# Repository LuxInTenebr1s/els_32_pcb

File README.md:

# els_32_pcb
ELS32 LED strip Ethernet controller with LAN8720 on PHY level.

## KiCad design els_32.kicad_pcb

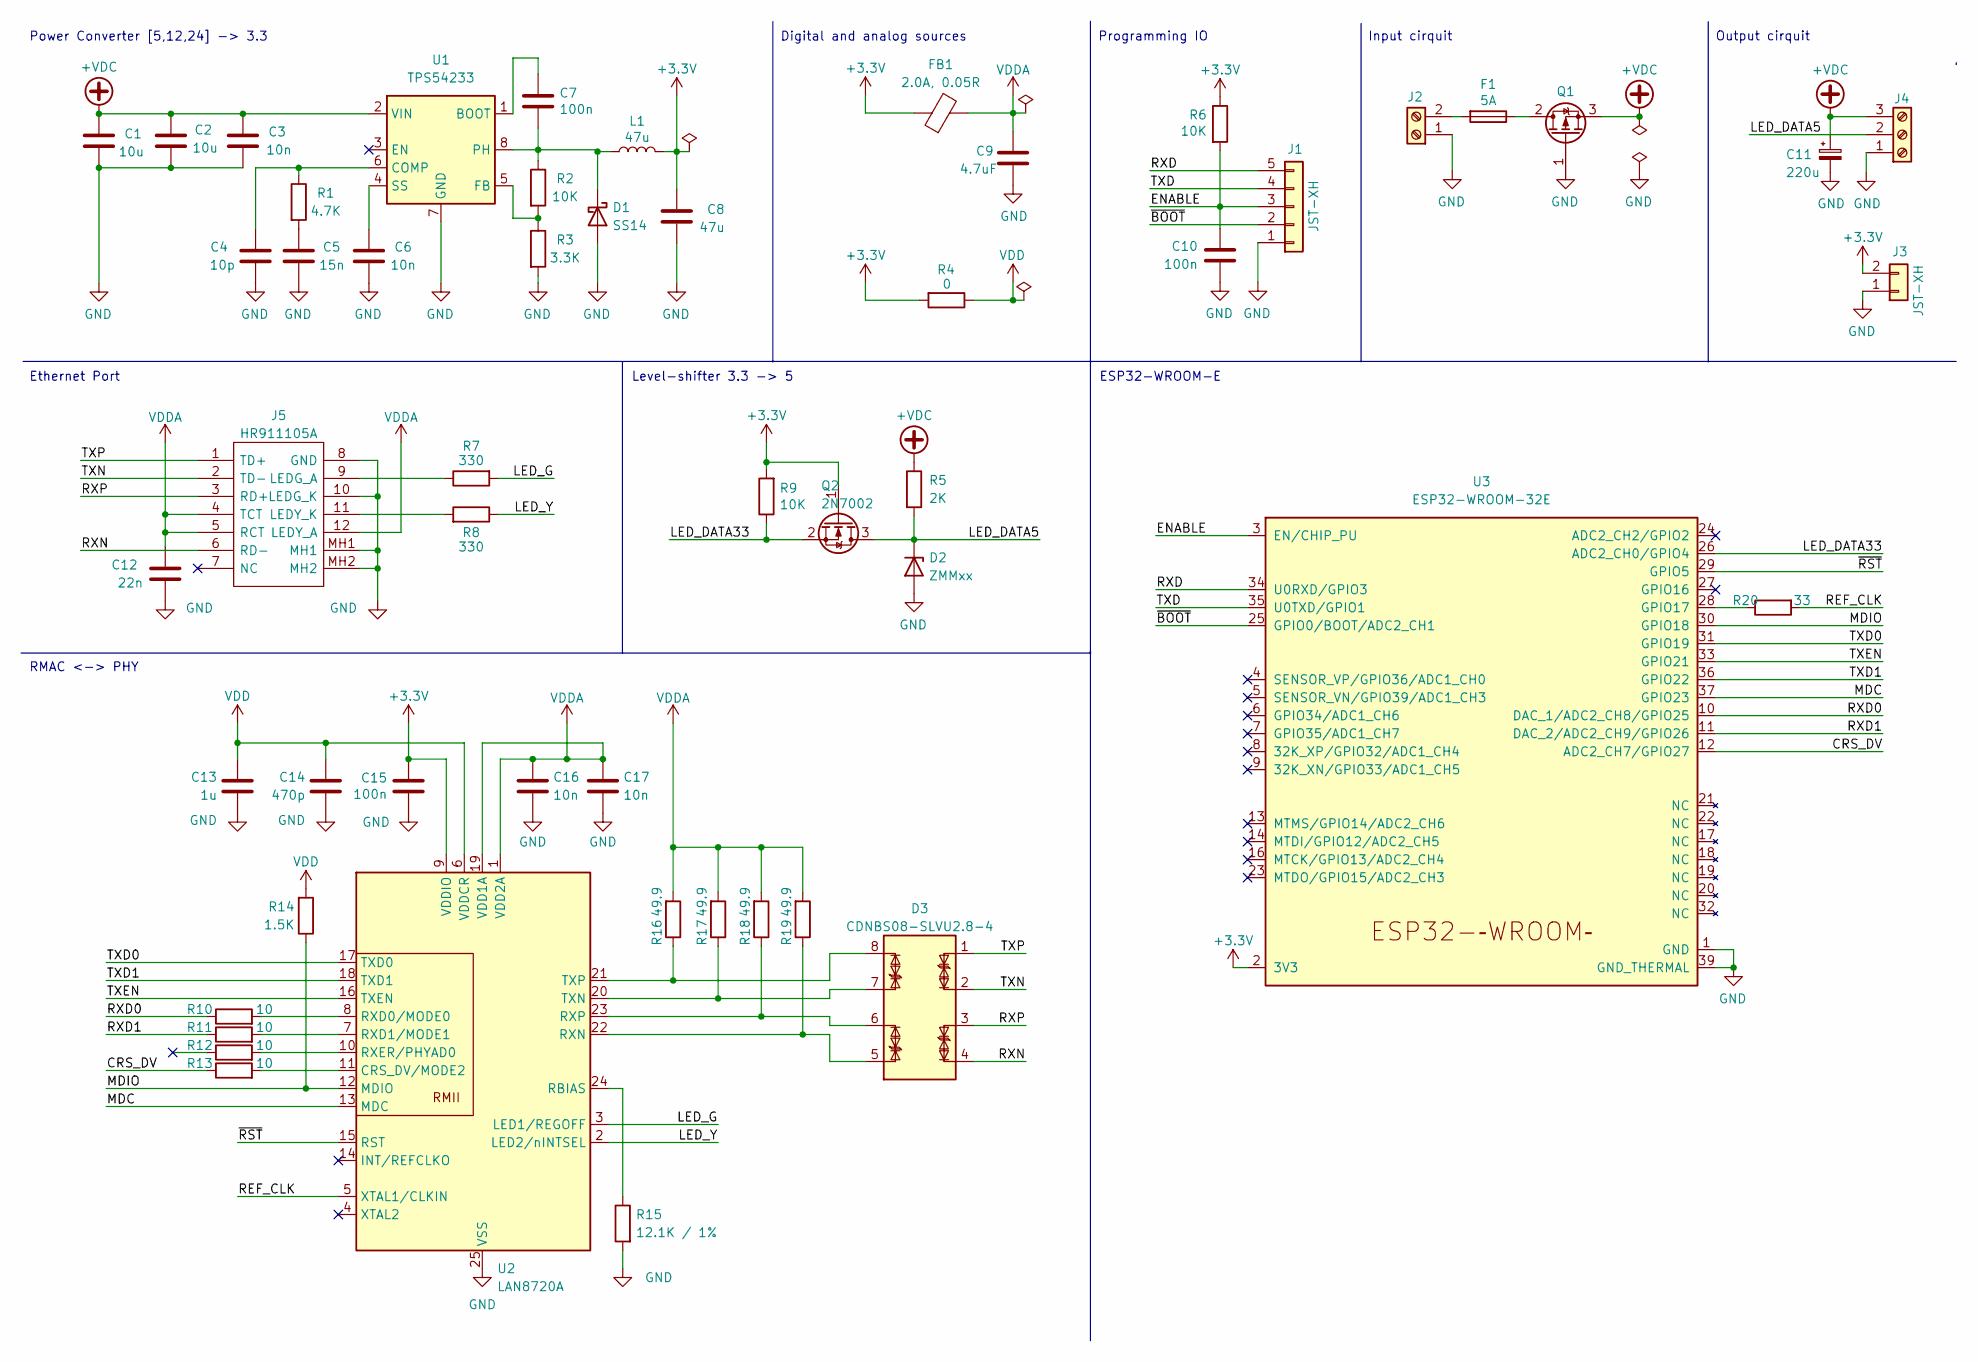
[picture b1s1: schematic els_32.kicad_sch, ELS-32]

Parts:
C1, C2: 10u; C_1206_3216Metric; LCSC C13585
C3, C6, C16, C17: 10n; C_0402_1005Metric; LCSC C15195
C4: 10p; C_0603_1608Metric; LCSC C1634
C5: 15n; C_0603_1608Metric; LCSC C1596
C7, C10, C15: 100n; C_0402_1005Metric; LCSC C307331
C8: 47u; C_1206_3216Metric; LCSC C96123
C9: 4.7uF; C_0402_1005Metric; LCSC C23733
C11: 220u; CP_Elec_6.3x7.7; LCSC C127327
C12: 22n; C_0402_1005Metric; LCSC C1532
C13: 1u; C_0402_1005Metric; LCSC C52923
C14: 470p; C_0402_1005Metric; LCSC C1537
D1: SS14; D_SMA; LCSC C2480
D2: ZMMxx; D_MiniMELF; LCSC C8062
D3: CDNBS08-SLVU2.8-4; SOIC-8_3.9x4.9mm_P1.27mm; LCSC C2841839
F1: 5A; Fuseholder_Littelfuse_Nano2_154x; LCSC C108518
FB1: 2.0A, 0.05R; R_0603_1608Metric; LCSC C275484
J1: JST-XH; JST_XH_B5B-XH-A_1x05_P2.50mm_Vertical
J2: WAGO; TerminalBlock_WAGO_236-102_1x02_P5.00mm_45Degree
J3: JST-XH; JST_XH_B2B-XH-AM_1x02_P2.50mm_Vertical
J4: Conn_01x03_Female; TerminalBlock_WAGO_236-103_1x03_P5.00mm_45Degree
J5: HR911105A; Manufacturer_Part_Number HR911105A; LCSC C12074
L1: 47u; L_Sunlord_MWSA06xxS; LCSC C408471
Q1: Q_PMOS_DGS; SOT-23; LCSC C20917
Q2: 2N7002; SOT-23; LCSC C8545
R1: 4.7K; R_0402_1005Metric; LCSC C25900
R2, R6, R9: 10K; R_0402_1005Metric; LCSC C25744
R3: 3.3K; R_0402_1005Metric; LCSC C25890
R4: 0; R_1206_3216Metric; LCSC C17888
R5: 2K; R_1206_3216Metric; LCSC C17944
R7, R8: 330; R_0402_1005Metric; LCSC C25104
R10, R11, R12, R13: 10; R_0402_1005Metric; LCSC C25077
R14: 1.5K; R_0402_1005Metric; LCSC C25867
R15: 12.1K / 1%; R_0402_1005Metric; LCSC C25852
R16, R17, R18, R19: 49.9; R_0402_1005Metric; LCSC C25120
R20: 33; R_0402_1005Metric; LCSC C25105
U1: TPS54233; SOIC-8_3.9x4.9mm_P1.27mm; LCSC C9865
U2: LAN8720A; QFN-24-1EP_4x4mm_P0.5mm_EP2.6x2.6mm; LCSC C17146
U3: ESP32-WROOM-32E; LCSC C701342

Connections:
+3.3V: C8.2, C15.1, FB1.1, J3.2, L1.2, Q2.1 (G), R4.2, R6.1, R9.2, U2.9 (VDDIO), U3.2 (3V3)
+VDC: C1.2, C2.1, C3.2, C11.1, J4.3, Q1.3 (S), R5.1, U1.2 (VIN)
/CRS_DV: R13.1, U3.12 (ADC2_CH7/GPIO27)
/ENABLE: C10.2, J1.3, R6.2, U3.3 (EN/CHIP_PU)
/LED_DATA5: D2.1 (K), J4.2, Q2.3 (D), R5.2
/LED_DATA33: Q2.2 (S), R9.1, U3.26 (ADC2_CH0/GPIO4)
/LED_G: R7.2, U2.3 (LED1/REGOFF)
/LED_Y: R8.1, U2.2 (LED2/nINTSEL)
/MDC: U2.13 (MDC), U3.37 (GPIO23)
/MDIO: R14.1, U2.12 (MDIO), U3.30 (GPIO18)
/REF_CLK: R20.2, U2.5 (XTAL1/CLKIN)
/RXD: J1.5, U3.34 (U0RXD/GPIO3)
/RXD0: R10.1, U3.10 (DAC_1/ADC2_CH8/GPIO25)
/RXD1: R11.1, U3.11 (DAC_2/ADC2_CH9/GPIO26)
/RXN: D3.4 (TVS2), J5.6 (RD-)
/RXP: D3.3 (TVS1), J5.3 (RD+)
/TXD: J1.4, U3.35 (U0TXD/GPIO1)
/TXD0: U2.17 (TXD0), U3.31 (GPIO19)
/TXD1: U2.18 (TXD1), U3.36 (GPIO22)
/TXEN: U2.16 (TXEN), U3.33 (GPIO21)
/TXN: D3.2 (TVS2), J5.2 (TD-)
/TXP: D3.1 (TVS1), J5.1 (TD+)
/~BOOT: J1.2, U3.25 (GPIO0/BOOT/ADC2_CH1)
/~RST: U2.15 (RST), U3.29 (GPIO5)
GND: C1.1, C2.2, C3.1, C4.1, C5.2, C6.1, C8.1, C9.1, C10.1, C11.2, C12.1, C13.2, C14.2, C15.2, C16.2, C17.2, D1.2 (A), D2.2 (A), J1.1, J2.1, J3.1, J4.1, J5.8 (GND), J5.10 (LEDG_K), J5.MH1, J5.MH2, Q1.1 (G), R3.2, R15.2, U1.7 (GND), U2.25 (VSS), U3.1 (GND), U3.15 (GND), U3.38 (GND), U3.39 (GND_THERMAL)
unnamed: C4.2, R1.1, U1.6 (COMP)
unnamed: C5.1, R1.2
unnamed: C6.2, U1.4 (SS)
unnamed: C7.1, U1.1 (BOOT)
unnamed: C7.2, D1.1 (K), L1.1, R2.1, U1.8 (PH)
unnamed: D3.5 (TVS1), R19.1, U2.22 (RXN)
unnamed: D3.6 (TVS2), R18.1, U2.23 (RXP)
unnamed: D3.7 (TVS1), R17.1, U2.20 (TXN)
unnamed: D3.8 (TVS2), R16.1, U2.21 (TXP)
unnamed: F1.1, Q1.2 (D)
unnamed: F1.2, J2.2
unnamed: J5.9 (LEDG_A), R7.1
unnamed: J5.11 (LEDY_K), R8.2
unnamed: R2.2, R3.1, U1.5 (FB)
unnamed: R10.2, U2.8 (RXD0/MODE0)
unnamed: R11.2, U2.7 (RXD1/MODE1)
unnamed: R12.2, U2.10 (RXER/PHYAD0)
unnamed: R13.2, U2.11 (CRS_DV/MODE2)
unnamed: R15.1, U2.24 (RBIAS)
unnamed: R20.1, U3.28 (GPIO17)
VDD: C13.1, C14.1, R4.1, R14.2, U2.6 (VDDCR)
VDDA: C9.2, C12.2, C16.1, C17.1, FB1.2, J5.4 (TCT), J5.5 (RCT), J5.12 (LEDY_A), R16.2, R17.2, R18.2, R19.2, U2.1 (VDD2A), U2.19 (VDD1A)

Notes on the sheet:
Power Converter [5,12,24] -> 3.3
Level-shifter 3.3 -> 5
Programming IO
Digital and analog sources
RMAC <-> PHY
ESP32-WROOM-E
Ethernet Port
Output cirquit
Input cirquit

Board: 2 copper layers, 53 parts (0 on the bottom side), 47 nets, no tracks yet.

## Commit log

2023-03-08 git: update .gitignore with extra rules:wq
2023-03-08 schematic: created initial schematic of the board
    Core components of the board:
    - ESP32-WROOM-32E
    - LAN8720
    - MP2307
    - LM3940
2023-03-24 Update schematic: v0.2
    - use TPS54321 for VDC -> 3.3V
    - use 5.6 zener for level-shifting
    - cleanup
2023-05-25 update save
